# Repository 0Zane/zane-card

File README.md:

# zane-card
My visit card made as a PCB

## schematic

## PCB layout

## PCB render

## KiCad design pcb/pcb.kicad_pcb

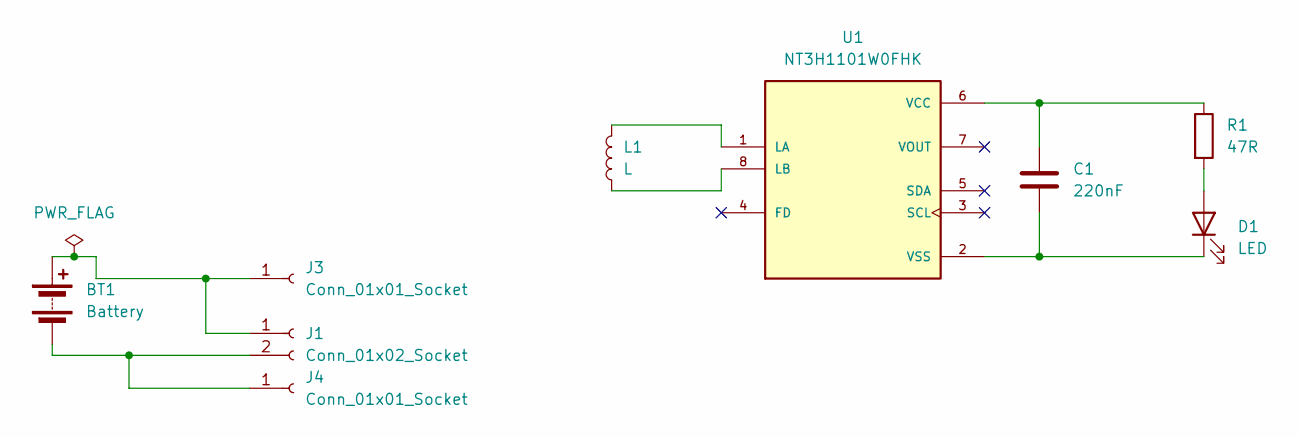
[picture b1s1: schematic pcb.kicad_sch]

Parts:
BT1: Battery; BatteryHolder_Keystone_3000_1x12mm
C1: 220nF; R_0603_2012Metric
D1: LED; LED_0603_1608Metric
J1: Conn_01x02_Socket; PinHeader_1x02_P1.00mm_Vertical
J3, J4: Conn_01x01_Socket; PinHeader_1x01_P1.00mm_Vertical
L1: L; nfcfallout
R1: 47R; LED_0603_2012Metric
U1: NT3H1101W0FHK; IC_NT3H1101W0FHK; PARTREV 3.3

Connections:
unnamed: BT1.1 (+), J1.1, J3.1 (Pin_1_1)
unnamed: BT1.2 (-), J1.2, J4.1 (Pin_1_1)
unnamed: D1.2 (A), R1.2
unnamed: C1.2, D1.1 (K), U1.2 (VSS)
unnamed: L1.2, U1.1 (LA)
unnamed: L1.1, U1.8 (LB)
unnamed: C1.1, R1.1, U1.6 (VCC)

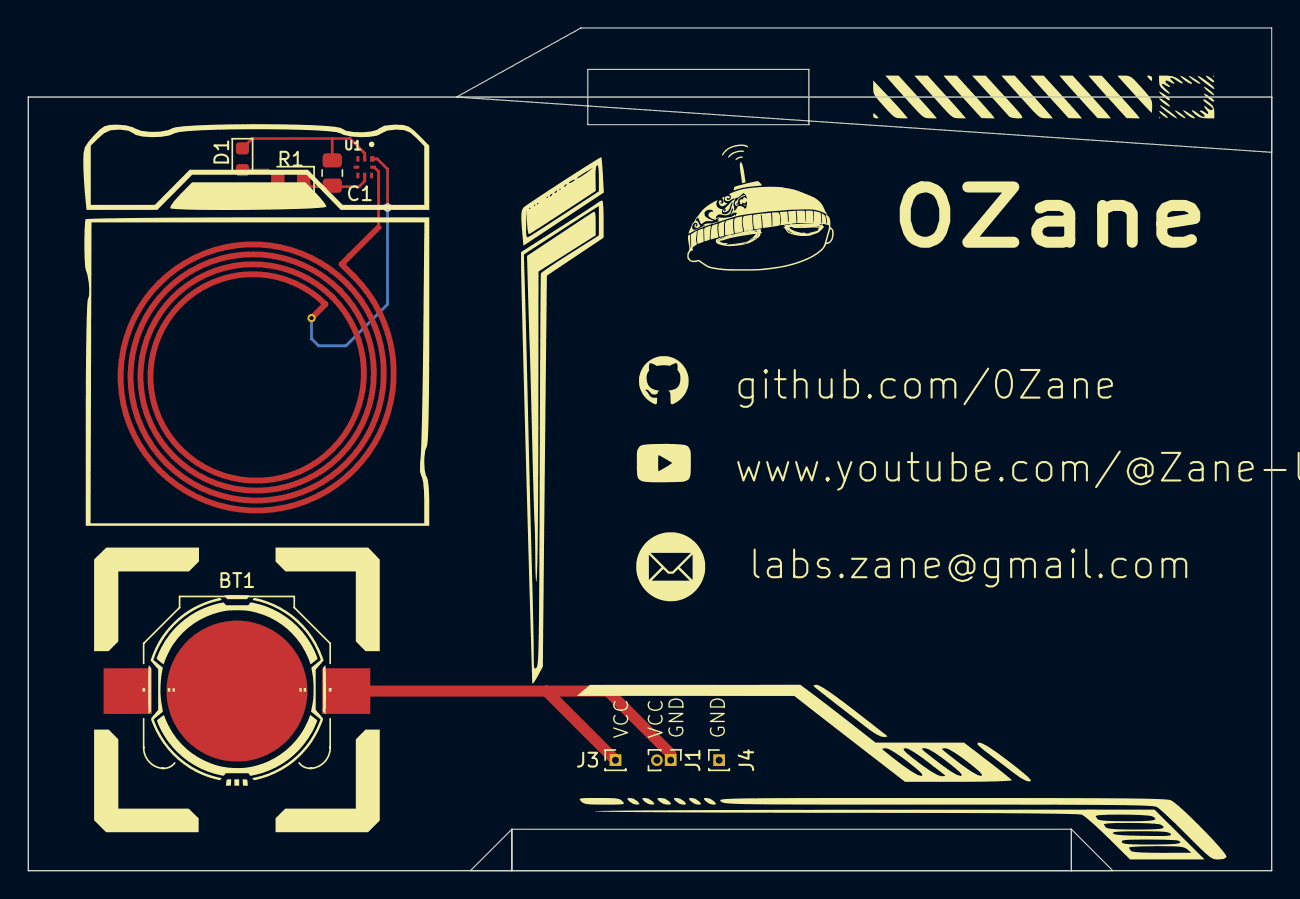
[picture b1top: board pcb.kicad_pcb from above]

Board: 2 copper layers, 90.0 x 61.0 mm, 9 parts (0 on the bottom side), 7 nets.

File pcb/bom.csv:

"Reference","Qty","Value","DNP","Exclude from BOM","Exclude from Board","Footprint","Datasheet"
"BT1","1","Battery","","","","Battery:BatteryHolder_Keystone_3000_1x12mm",""
"C1","1","220nF","","","","Capacitor_SMD:C_0603_1608Metric",""
"D1","1","LED","","","","LED_SMD:LED_0603_1608Metric",""
"J1","1","Conn_01x02_Socket","","","","Connector_PinHeader_1.00mm:PinHeader_1x02_P1.00mm_Vertical",""
"J3,J4","2","Conn_01x01_Socket","","","","Connector_PinHeader_1.00mm:PinHeader_1x01_P1.00mm_Vertical",""
"L1","1","L","","","","nfc:nfcfallout",""
"R1","1","47R","","","","Resistor_SMD:R_0603_1608Metric",""
"U1","1","NT3H1101W0FHK","","","","NT3H1101W0FHK:IC_NT3H1101W0FHK",""
